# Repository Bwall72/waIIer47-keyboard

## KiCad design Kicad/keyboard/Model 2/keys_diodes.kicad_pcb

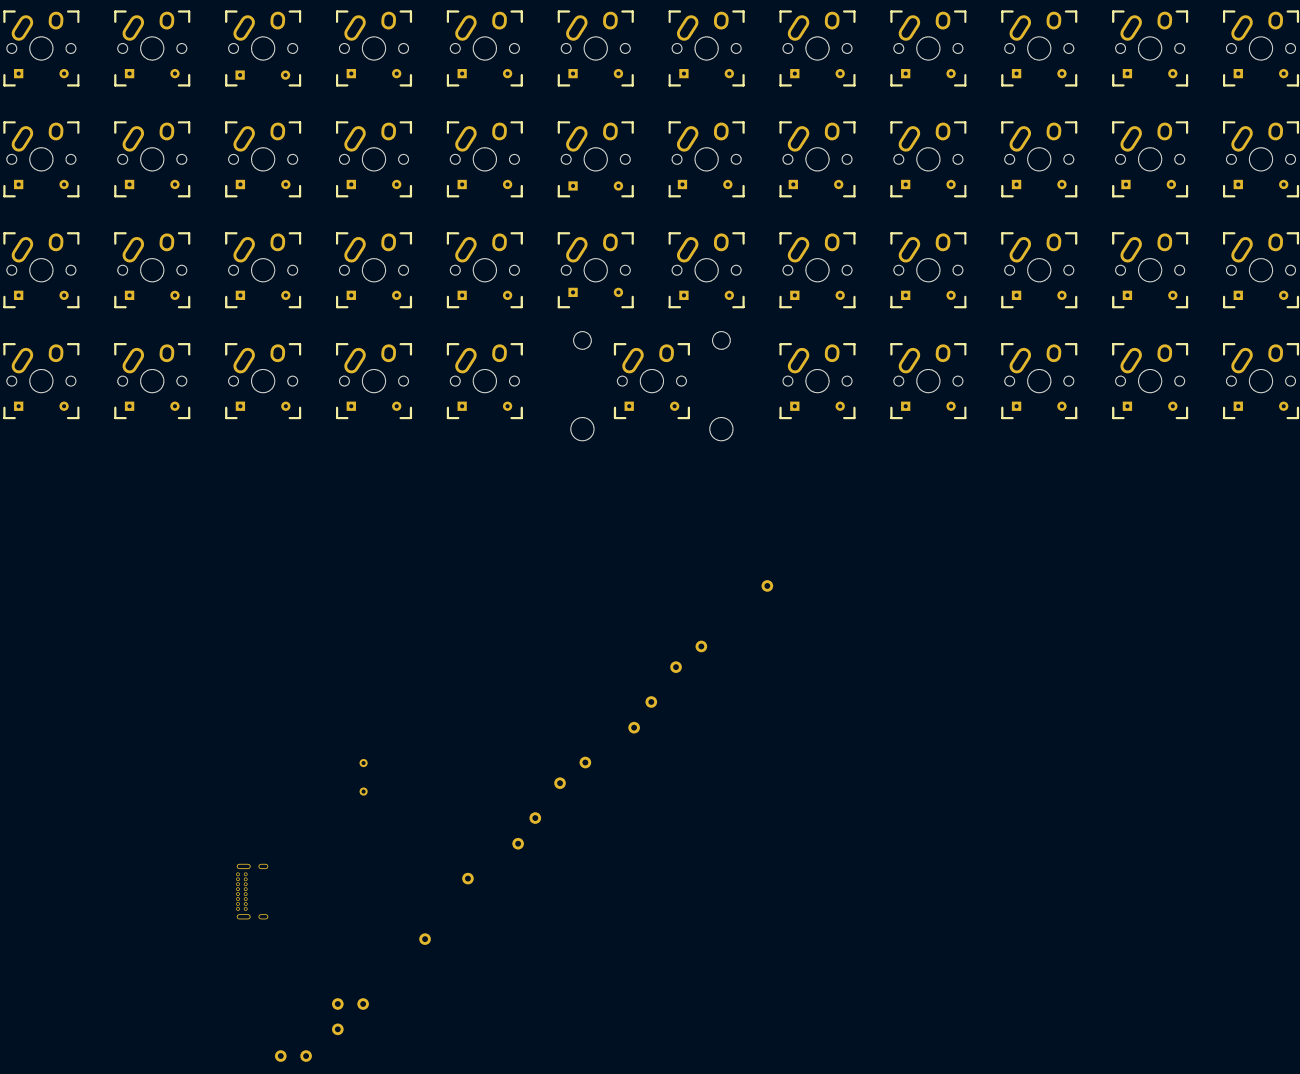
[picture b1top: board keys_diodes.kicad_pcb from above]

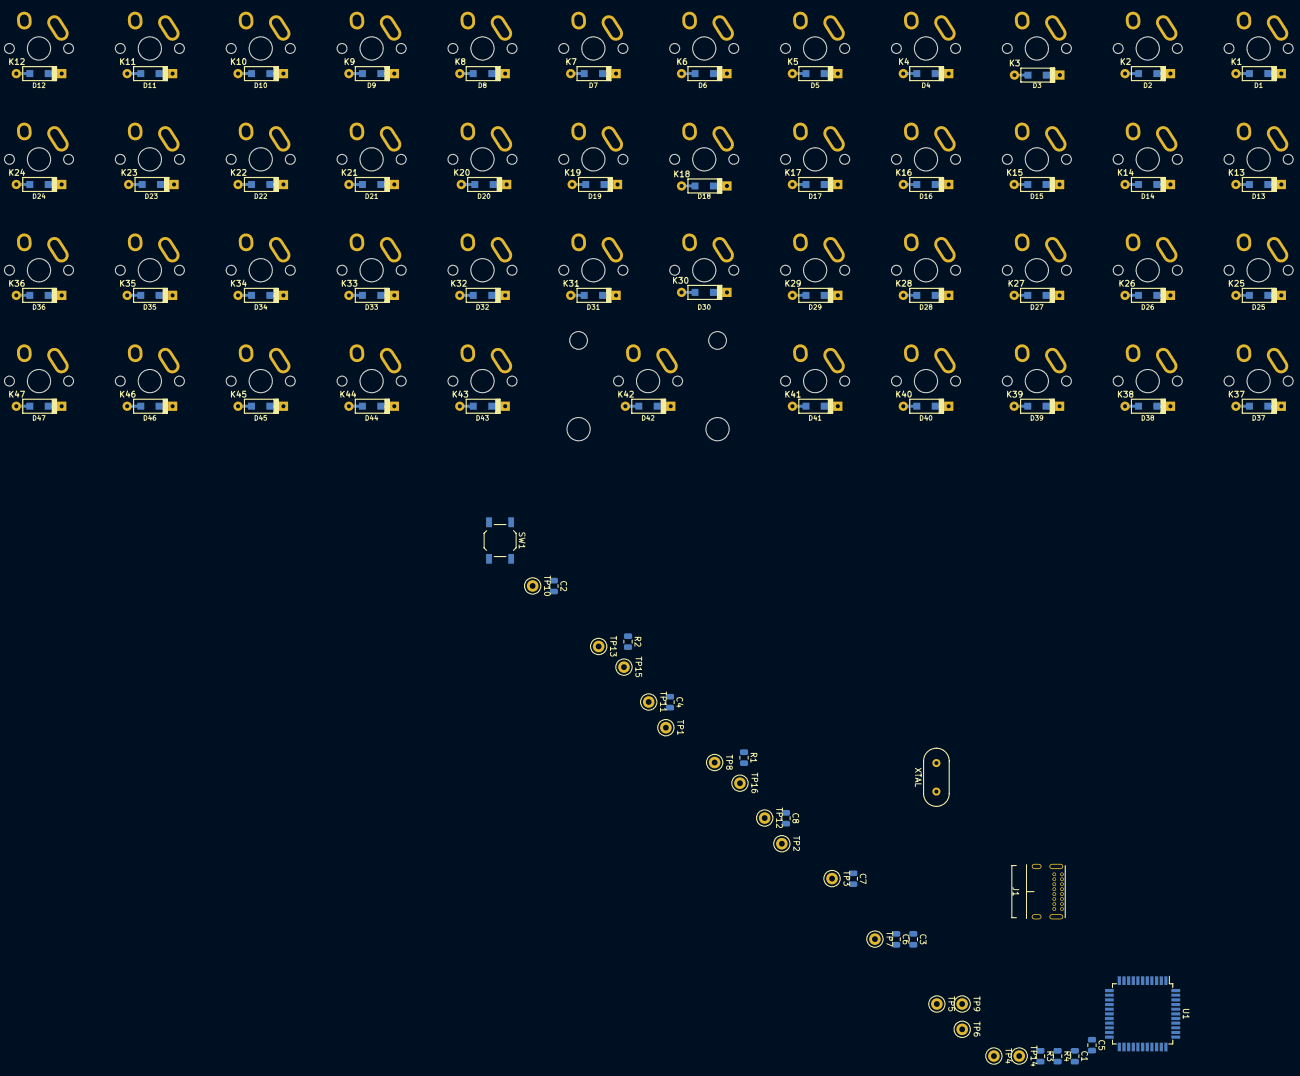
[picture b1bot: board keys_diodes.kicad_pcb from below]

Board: 2 copper layers, 126 parts (79 on the bottom side), 74 nets, no tracks yet.

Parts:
C1, C2: 22pF; C_0805_2012Metric
C3, C4, C5, C6, C7: 0.1uF; C_0805_2012Metric
C8: 1uF; C_0805_2012Metric
D1, D2, D3, D4, D5, D6, D7, D8, D9, D10, D11, D12, D13, D14, D15, D16, D17, D18, D19, D20, D21, D22, D23, D24, D25, D26, D27, D28, D29, D30, D31, D32, D33, D34, D35, D36, D37, D38, D39, D40, D41, D42, D43, D44, D45, D46, D47: D; D_SOD123_axial
J1: USB_C_Receptacle_USB2.0; USB_C_GCT_USB4085
K1, K2, K3, K4, K5, K6, K7, K8, K9, K10, K11, K12, K13, K14, K15, K16, K17, K18, K19, K20, K21, K22, K23, K24, K25, K26, K27, K28, K29, K30, K31, K32, K33, K34, K35, K36, K37, K38, K39, K40, K41, K43, K44, K45, K46, K47: KEYSW; Mx_Alps_100
K42: KEYSW; Mx_Alps_200
R1, R2: 10k; R_0805_2012Metric
R3, R4: 22; R_0805_2012Metric
SW1: SW_PUSH; SW_SPST_TL3342
TP1, TP2, TP3, TP4, TP5, TP6, TP7, TP8, TP9, TP10, TP11, TP12, TP13, TP14, TP15, TP16: TestPoint; TestPoint_Keystone_5000-5004_Miniature
U1: ATMEGA32U4; TQFP-44_10x10mm_P0.8mm
X1: XTAL; XTAL_HC_49_TH

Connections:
/col0: K1.1, K13.1, K25.1, K37.1, TP5.1, U1.25
/col1: K2.1, K14.1, K26.1, K38.1, TP6.1, U1.31
/col2: K3.1, K15.1, K27.1, K39.1, TP7.1, U1.30
/col3: K4.1, K16.1, K28.1, K40.1, TP8.1, U1.29
/col4: K5.1, K17.1, K29.1, K41.1, TP9.1, U1.28
/col5: K6.1, K18.1, K30.1, TP10.1, U1.27
/col6: K7.1, K19.1, K31.1, K42.1, TP11.1, U1.26
/col7: K8.1, K20.1, K32.1, K43.1, TP12.1, U1.32
/col8: K9.1, K21.1, K33.1, K44.1, TP13.1, U1.18
/col9: K10.1, K22.1, K34.1, K45.1, TP14.1, U1.19
/col10: K11.1, K23.1, K35.1, K46.1, TP15.1, U1.20
/col11: K12.1, K24.1, K36.1, K47.1, TP16.1, U1.21
/row0: D1.1, D2.1, D3.1, D4.1, D5.1, D6.1, D7.1, D8.1, D9.1, D10.1, D11.1, D12.1, TP1.1, U1.41
/row1: D13.1, D14.1, D15.1, D16.1, D17.1, D18.1, D19.1, D20.1, D21.1, D22.1, D23.1, D24.1, TP2.1, U1.40
/row2: D25.1, D26.1, D27.1, D28.1, D29.1, D30.1, D31.1, D32.1, D33.1, D34.1, D35.1, D36.1, TP3.1, U1.39
/row3: D37.1, D38.1, D39.1, D40.1, D41.1, D42.1, D43.1, D44.1, D45.1, D46.1, D47.1, TP4.1, U1.38
GND: C1.2, C2.2, C3.2, C4.2, C5.2, C6.2, C7.2, C8.1, J1.A1, J1.A12, J1.B1, J1.B12, J1.S1, R2.1, SW1.1, U1.5, U1.15, U1.23, U1.35, U1.43
unnamed: C1.1, U1.17, X1.1
unnamed: C2.1, U1.16, X1.2
unnamed: C8.2, U1.6
unnamed: D1.2, K1.2
unnamed: D2.2, K2.2
unnamed: D3.2, K3.2
unnamed: D4.2, K4.2
unnamed: D5.2, K5.2
unnamed: D6.2, K6.2
unnamed: D7.2, K7.2
unnamed: D8.2, K8.2
unnamed: D9.2, K9.2
unnamed: D10.2, K10.2
unnamed: D11.2, K11.2
unnamed: D12.2, K12.2
unnamed: D13.2, K13.2
unnamed: D14.2, K14.2
unnamed: D15.2, K15.2
unnamed: D16.2, K16.2
unnamed: D17.2, K17.2
unnamed: D18.2, K18.2
unnamed: D19.2, K19.2
unnamed: D20.2, K20.2
unnamed: D21.2, K21.2
unnamed: D22.2, K22.2
unnamed: D23.2, K23.2
unnamed: D24.2, K24.2
unnamed: D25.2, K25.2
unnamed: D26.2, K26.2
unnamed: D27.2, K27.2
unnamed: D28.2, K28.2
unnamed: D29.2, K29.2
unnamed: D30.2, K30.2
unnamed: D31.2, K31.2
unnamed: D32.2, K32.2
unnamed: D33.2, K33.2
unnamed: D34.2, K34.2
unnamed: D35.2, K35.2
unnamed: D36.2, K36.2
unnamed: D37.2, K37.2
unnamed: D38.2, K38.2
unnamed: D39.2, K39.2
unnamed: D40.2, K40.2
unnamed: D41.2, K41.2
unnamed: D42.2, K42.2
unnamed: D43.2, K43.2
unnamed: D44.2, K44.2
unnamed: D45.2, K45.2
unnamed: D46.2, K46.2
unnamed: D47.2, K47.2
unnamed: J1.A6, J1.B6, R4.2
unnamed: J1.A7, J1.B7, R3.2
unnamed: R1.1, SW1.2, U1.13
unnamed: R2.2, U1.33
unnamed: R3.1, U1.3
unnamed: R4.1, U1.4
VCC: C3.1, C4.1, C5.1, C6.1, C7.1, J1.A4, J1.A9, J1.B4, J1.B9, R1.2, U1.2, U1.7, U1.14, U1.24, U1.34, U1.44
